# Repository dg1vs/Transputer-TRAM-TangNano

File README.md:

# Transputer-TRAM-TangNano

A **TRAM-size FPGA Transputer module** based on the **Sipeed Tang Nano 20K**.

The goal of this project is to provide a modern, compact Transputer module which can be used in systems designed for classic INMOS TRAMs, while replacing most of the increasingly difficult-to-obtain historical hardware with an FPGA implementation.

The project targets FPGA implementations of the **T805** and **T425** Transputers and is intended both for practical use in existing Transputer systems and for experimenting with Transputer hardware today.

The main idea behind this project is to provide a TRAM with an FPGA based implementation. For FPGA imlemetation please see the paper [1]. 

## Main Features

- TRAM-size PCB
- Sipeed **Tang Nano 20K** FPGA module
- FPGA implements the **INMOS T805 and T425**
- Standard Transputer link interface
- Four Transputer links
- Support for the usual TRAM control signals
- 5 V / 3.3 V level adaptation between classic Transputer hardware and the FPGA
- I²S audio support
- Selected Transputer and FPGA signals available on pin headers
- Can be used in systems with standard TRAM slots, including the **ATW800/2**
- Ready-to-program Gowin `.fs` FPGA image available

## Background

Original Transputer systems are still interesting platforms for experimenting with parallel computing, message-passing architectures and historical computer hardware.

One problem when building or restoring such systems is the availability of suitable Transputer processors and associated interface components.

At the same time, inexpensive modern FPGA modules such as the **Tang Nano 20K** provide enough resources to implement a Transputer together with additional peripheral logic in a very small form factor.

The idea behind **Transputer-TRAM-TangNano** is therefore simple:

> Put a modern FPGA implementation of a Transputer into the mechanical and electrical environment of a classic TRAM.

This makes it possible to use the module together with existing Transputer hardware without requiring another custom host interface.

## FPGA Transputer

The Tang Nano 20K carries the FPGA implementation of the Transputer.

The T425 is representative of the widely used 32-bit integer Transputers, while the T805 adds floating-point capabilities and was one of the most powerful members of the classic Transputer family.

The FPGA implementation used by this project is based on joint work by **Andre** , **Claus (cpm)** and **me (dg1vs)**.

### FPGA source code

A ready-to-program **Gowin `.fs` bitstream file** is available.

The FPGA HDL source code itself is currently **not published** as part of this repository.

This means that the supplied FPGA image can be used to operate the hardware, but rebuilding or modifying the FPGA design requires access to the original FPGA sources.

## TRAM Interface

The module follows the basic interface concept of a classic Transputer TRAM.

The hardware provides the four standard Transputer communication links:

- Link 0
- Link 1
- Link 2
- Link 3

Each link consists of a `LinkIn` and `LinkOut` signal.

The TRAM interface also provides the normal Transputer control signals including:

- `ClockIn`
- `Analyse`
- `Reset`
- `notError`
- Link-speed is set fixed to 20 Mbps

This allows the FPGA-based Transputer to behave like a conventional Transputer module from the point of view of the host system.

## 5 V / 3.3 V Level Adaptation

One of the less obvious challenges when combining original Transputer hardware with a modern FPGA is the difference in logic levels.

Classic TRAM and Transputer hardware operates in a **5 V environment**, while the Tang Nano 20K and its FPGA I/O use **3.3 V logic**.

Considerable attention was therefore given to the interface between these two voltage domains.

The current hardware design uses dedicated level-translation circuitry for the Transputer links. Four **TXU0202 dual-channel level translators** provide the eight signal paths required for the four `LinkIn` / `LinkOut` pairs.

Additional circuitry is used for the Transputer control, clock and status signals.

The intention is to make the module compatible with real Transputer hardware while protecting the modern FPGA from inappropriate signal levels.

## Breakout Connectors

Several signals are additionally available on 2.54 mm pin headers.

These connectors are useful for:

- Sound interface (quite cool for an transputer)
- debugging
- logic-analyzer measurements
- FPGA experiments
- connecting additional peripherals
- accessing selected Transputer signals
- experimenting with Transputer links

The PCB contains dedicated connectors for link, event and audio-related signals.

This makes the board useful not only as a replacement TRAM but also as a development platform for Transputer experiments.

## Audio / I²S

Audio output is supported using the **I²S/PCM facilities of the Tang Nano 20K**.

The Tang Nano 20K contains onboard audio hardware, and the TRAM carrier additionally provides an audio connector for access to the relevant signals.

This allows Transputer or FPGA applications to generate sound without requiring a separate audio subsystem.

## ATW800/2

The module can be used with the **ATW800/2** Atari Transputer system.

The ATW800/2 provides conventional size-1 TRAM slots for physical Transputer modules, making the Transputer-TRAM-TangNano a natural companion for this system.

## Hardware

The PCB was designed with **KiCad**.

The main project files are located in:

```text
hardware/tram_tangnano/
    tram_tangnano.kicad_pro
    tram_tangnano.kicad_sch
    tram_tangnano.kicad_pcb
```

The project uses the separate **Transputer-Kicad-Library** as a Git submodule:

```text
hardware/libs/Transputer-Kicad-Library
```

After cloning the repository, initialize the submodule with:

```bash
git submodule update --init --recursive
```

## FPGA Programming

The supplied `.fs` file is a ready-to-program Gowin FPGA bitstream for the Tang Nano 20K.

It can be programmed using the usual Tang Nano 20K programming tools, for example:

- Gowin Programmer
- openFPGALoader

The FPGA source project is currently not included in this repository.

## Project Status

This is an experimental retro-computing hardware project.

The board has already gone through several hardware revisions, particularly around the 5 V / 3.3 V interface.

See `CHANGELOG.md` for known issues and changes between PCB revisions.

When building a board, always check the current schematic, PCB revision and changelog before ordering PCBs or assembling components.

## Credits

- **Andre**
- **Claus (cpm)**

## References

A useful technical background reference for implementing the Transputer architecture in an FPGA is:

[1] Uwe, Mielke & Martin, Zabel & Michael, Bruestle. (2019). T42 – Transputer in FPGA. 10.3233/978-1-61499-949-2-525.

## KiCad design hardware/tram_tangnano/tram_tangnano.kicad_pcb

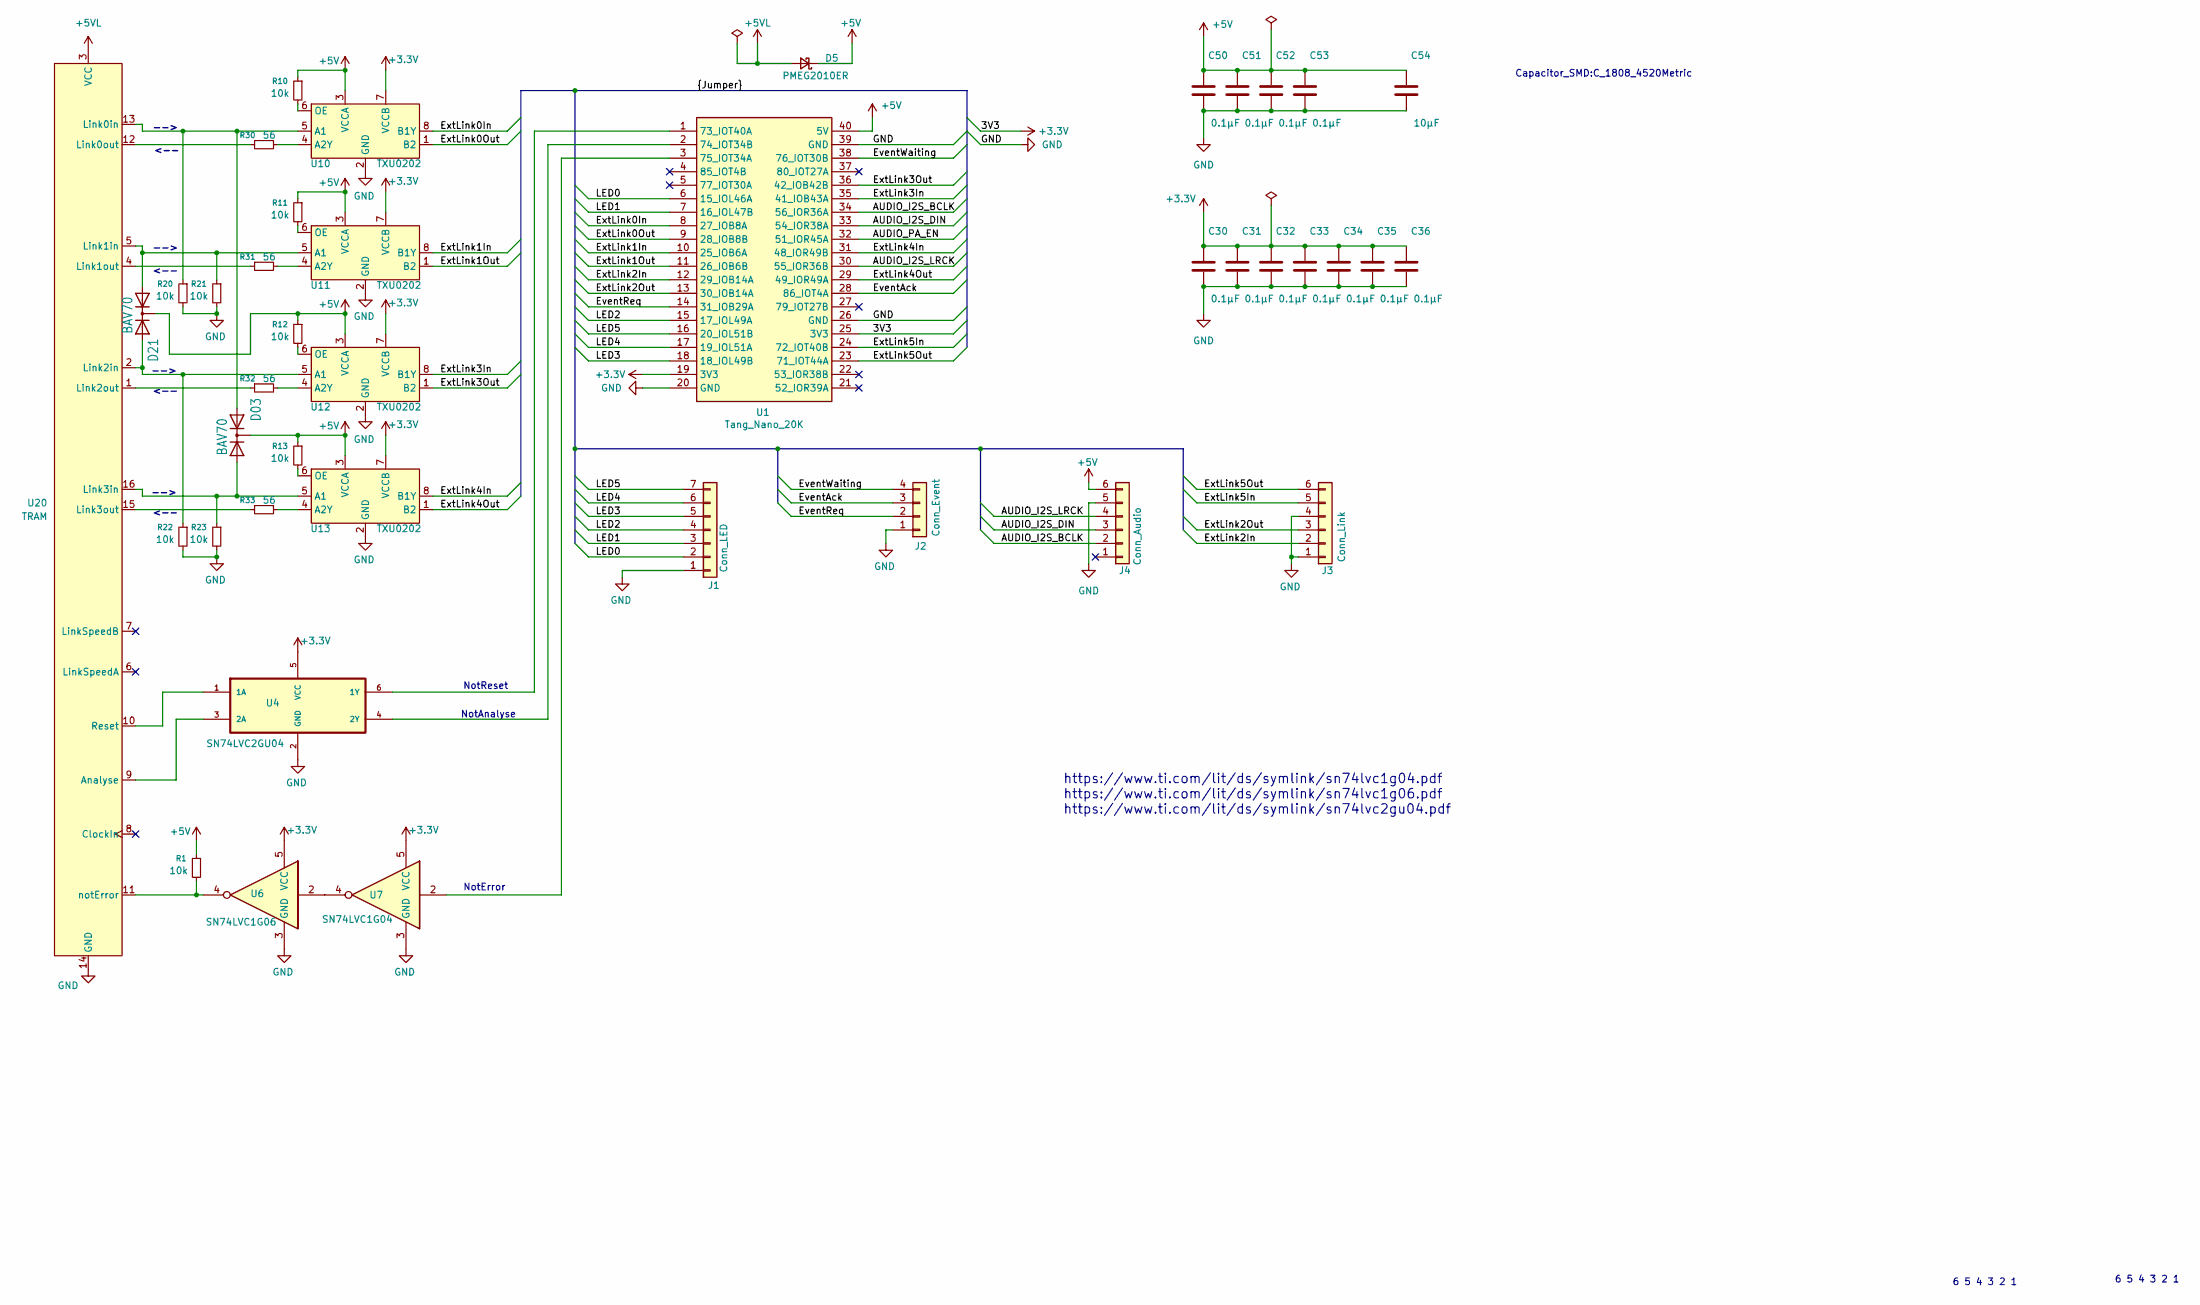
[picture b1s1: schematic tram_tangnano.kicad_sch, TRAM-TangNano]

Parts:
C30, C31, C32, C33, C34, C35, C36, C50, C51, C52, C53: 0.1µF; C_0603_1608Metric_Pad1.08x0.95mm_HandSolder; LCSC C14663
C54: 10µF; C_Elec_3x5.4
D03, D21: BAV70; SOT-23; LCSC C68978
D5: PMEG2010ER; Nexperia_CFP3_SOD-123W
J1: Conn_LED; PinHeader_1x07_P2.54mm_Vertical
J2: Conn_Event; PinHeader_1x04_P2.54mm_Vertical
J3: Conn_Link; PinHeader_1x06_P2.54mm_Vertical
J4: Conn_Audio; PinHeader_1x06_P2.54mm_Vertical
R1, R10, R11, R12, R13, R20, R21, R22, R23: 10k; R_0603_1608Metric_Pad0.98x0.95mm_HandSolder; LCSC C25804
R30, R31, R32, R33: 56; R_0603_1608Metric_Pad0.98x0.95mm_HandSolder; LCSC C25196
U1: Tang_Nano_20K; DIP-40_TangNano20K
U4: SN74LVC2GU04; SOT-23-6_Handsoldering; LCSC C41430939
U6: SN74LVC1G06; SOT-23-5_HandSoldering; LCSC C22469967
U7: SN74LVC1G04; SOT-23-5_HandSoldering; LCSC C19829658
U10, U11, U12, U13: TXU0202; VSSOP-8_2.3x2mm_P0.5mm; LCSC C7372013
U20: TRAM; TRAM-1-PCB

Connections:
+3.3V: C30.1, C31.1, C32.1, C33.1, C34.1, C35.1, C36.1, U1.19 (3V3), U1.25 (3V3), U4.5 (VCC), U6.5 (VCC), U7.5 (VCC), U10.7 (VCCB), U11.7 (VCCB), U12.7 (VCCB), U13.7 (VCCB)
+5V: C50.1, C51.1, C52.1, C53.1, C54.1, D03.3 (C), D5.1 (K), D21.3 (C), J4.6, R1.1, R10.1, R11.1, R12.1, R13.1, U1.40 (5V), U10.3 (VCCA), U11.3 (VCCA), U12.3 (VCCA), U13.3 (VCCA)
+5VL: D5.2 (A), U20.3 (VCC)
/AUDIO_I2S_BCLK: J4.2, U1.34 (56_IOR36A)
/AUDIO_I2S_DIN: J4.3, U1.33 (54_IOR38A)
/AUDIO_I2S_LRCK: J4.4, U1.30 (55_IOR36B)
/AUDIO_PA_EN: U1.32 (51_IOR45A)
/EventAck: J2.3, U1.28 (86_IOT4A)
/EventReq: J2.2, U1.14 (31_IOB29A)
/EventWaiting: J2.4, U1.38 (76_IOT30B)
/ExtLink0In: U1.8 (27_IOB8A), U10.8 (B1Y)
/ExtLink0Out: U1.9 (28_IOB8B), U10.1 (B2)
/ExtLink1In: U1.10 (25_IOB6A), U11.8 (B1Y)
/ExtLink1Out: U1.11 (26_IOB6B), U11.1 (B2)
/ExtLink2In: J3.2, U1.12 (29_IOB14A)
/ExtLink2Out: J3.3, U1.13 (30_IOB14A)
/ExtLink3In: U1.35 (41_IOB43A), U12.8 (B1Y)
/ExtLink3Out: U1.36 (42_IOB42B), U12.1 (B2)
/ExtLink4In: U1.31 (48_IOR49B), U13.8 (B1Y)
/ExtLink4Out: U1.29 (49_IOR49A), U13.1 (B2)
/ExtLink5In: J3.5, U1.24 (72_IOT40B)
/ExtLink5Out: J3.6, U1.23 (71_IOT44A)
/LED0: J1.2, U1.6 (15_IOL46A)
/LED1: J1.3, U1.7 (16_IOL47B)
/LED2: J1.4, U1.15 (17_IOL49A)
/LED3: J1.5, U1.18 (18_IOL49B)
/LED4: J1.6, U1.17 (19_IOL51A)
/LED5: J1.7, U1.16 (20_IOL51B)
GND: C30.2, C31.2, C32.2, C33.2, C34.2, C35.2, C36.2, C50.2, C51.2, C52.2, C53.2, C54.2, J1.1, J2.1, J3.1, J3.4, J4.5, R20.2, R21.2, R22.2, R23.2, U1.20 (GND), U1.26 (GND), U1.39 (GND), U4.2 (GND), U6.3 (GND), U7.3 (GND), U10.2 (GND), U11.2 (GND), U12.2 (GND), U13.2 (GND), U20.14 (GND)
unnamed: D03.1 (A1), R23.1, U13.5 (A1), U20.16 (Link3in)
unnamed: D03.2 (A2), R20.1, U10.5 (A1), U20.13 (Link0in)
unnamed: D21.1 (A1), R22.1, U12.5 (A1), U20.2 (Link2in)
unnamed: D21.2 (A2), R21.1, U11.5 (A1), U20.5 (Link1in)
unnamed: U1.1 (73_IOT40A), U4.6 (1Y)
unnamed: U1.2 (74_IOT34B), U4.4 (2Y)
unnamed: U1.3 (75_IOT34A), U7.2
unnamed: U6.2, U7.4
unnamed: R30.2, U10.4 (A2Y)
unnamed: R10.2, U10.6 (OE)
unnamed: R31.2, U11.4 (A2Y)
unnamed: R11.2, U11.6 (OE)
unnamed: R32.2, U12.4 (A2Y)
unnamed: R12.2, U12.6 (OE)
unnamed: R33.2, U13.4 (A2Y)
unnamed: R13.2, U13.6 (OE)
unnamed: U4.3 (2A), U20.9 (Analyse)
unnamed: R30.1, U20.12 (Link0out)
unnamed: R31.1, U20.4 (Link1out)
unnamed: R32.1, U20.1 (Link2out)
unnamed: R33.1, U20.15 (Link3out)
unnamed: U4.1 (1A), U20.10 (Reset)
unnamed: R1.2, U6.4, U20.11 (notError)

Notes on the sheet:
-->
6 5 4 3 2 1
https://www.ti.com/lit/ds/symlink/sn74lvc1g04.pdf https://www.ti.com/lit/ds/symlink/sn74lvc1g06.pdf https://www.ti.com/lit/ds/symlink/sn74lvc2gu04.pdf
<--
Capacitor_SMD:C_1808_4520Metric
NotReset
NotAnalyse
NotError

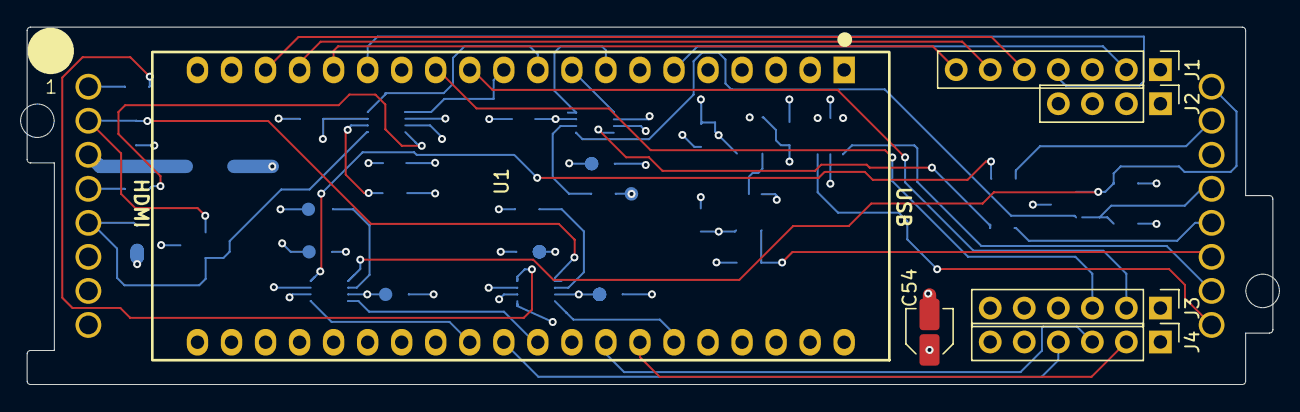
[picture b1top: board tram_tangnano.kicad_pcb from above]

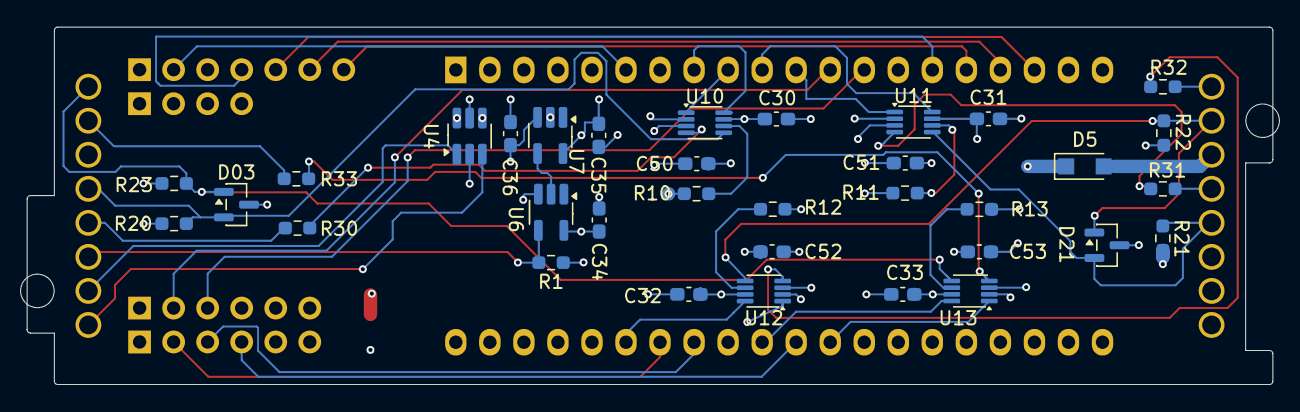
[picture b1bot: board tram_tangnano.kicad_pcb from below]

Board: 4 copper layers, 93.0 x 26.7 mm, 41 parts (34 on the bottom side), 51 nets.

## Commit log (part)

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2026-05-27 Init
2026-05-27 Version
2026-06-03 Change to 10.x
2026-06-03 Lib added
2026-06-03 Update Lib
2026-06-06 temp
